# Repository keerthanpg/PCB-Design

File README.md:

# PCB-Design

Files for our implementation of an electronic 2DOF face tracker

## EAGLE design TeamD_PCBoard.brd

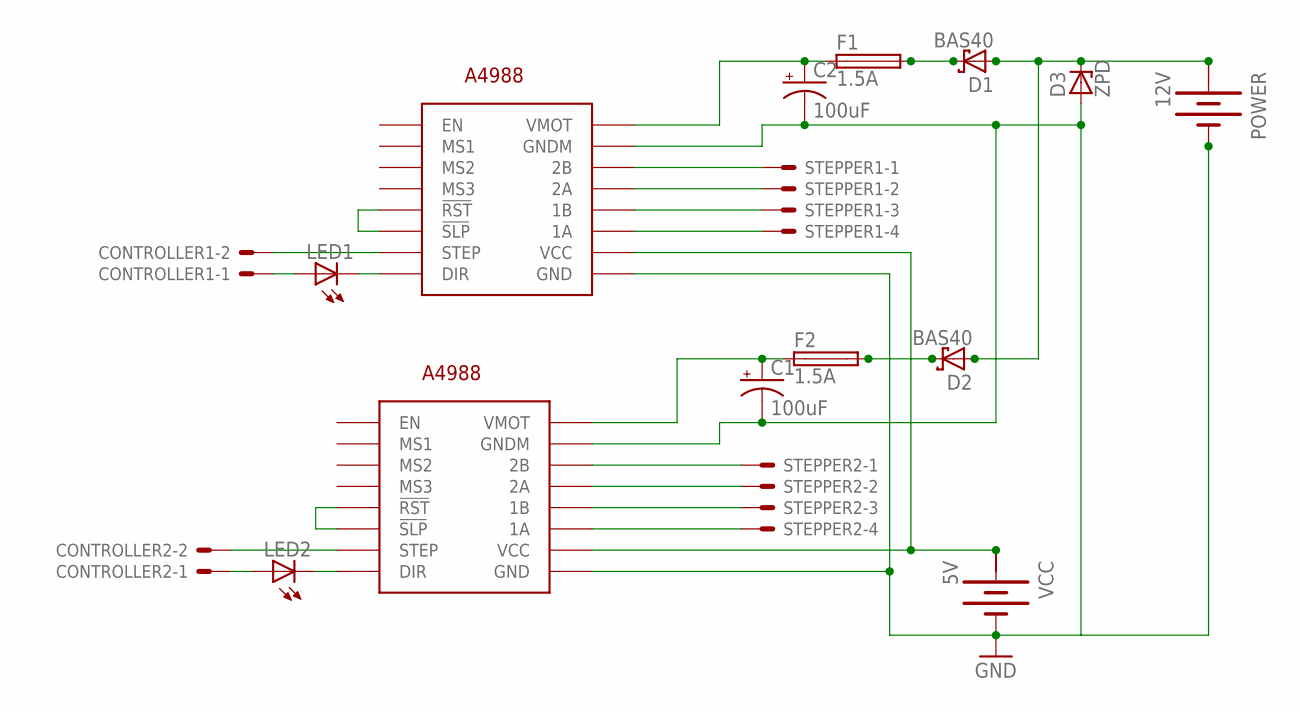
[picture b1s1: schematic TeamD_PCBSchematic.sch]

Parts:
C1, C2: 100uF; E15-5
CONTROLLER1, CONTROLLER2: 22-23-2021
D1, D2: BAS40; SOT23
D3: ZPD; DO35Z10
F1, F2: 1.5A; 19559
LED1, LED2: LED; SMARTLED-TTW
POWER: 12V; BATTERY
STEPPER1, STEPPER2: 22-23-2041
U$1, U$2: STEP-STICK
VCC: 5V; BATTERY

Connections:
+: POWER.+@1 (+), VCC.+@1 (+)
unnamed: CONTROLLER1.2, U$1.SPT (STEP)
unnamed: CONTROLLER2.2, U$2.SPT (STEP)
unnamed: CONTROLLER2.1, LED2.A@1 (A)
unnamed: U$1.RST (!RST), U$1.SLP (!SLP)
unnamed: U$2.RST (!RST), U$2.SLP (!SLP)
unnamed: STEPPER2.1, U$2.2B
unnamed: STEPPER2.2, U$2.2A
unnamed: STEPPER2.3, U$2.1B
unnamed: STEPPER2.4, U$2.1A
unnamed: STEPPER1.1, U$1.2B
unnamed: STEPPER1.2, U$1.2A
unnamed: STEPPER1.3, U$1.1B
unnamed: STEPPER1.4, U$1.1A
unnamed: D1.3 (C), F1.2
unnamed: LED1.C@1 (C), U$1.DIR
unnamed: LED2.C@1 (C), U$2.DIR
unnamed: C2.+, F1.1, U$1.VMOT
unnamed: C1.+, F2.1, U$2.VMOT
unnamed: U$1.VCC, U$2.VCC, VCC.+
unnamed: D2.3 (C), F2.2
unnamed: D1.1 (A), D2.1 (A), D3.C, POWER.+
unnamed: C1.-, C2.-, D3.A, POWER.-, U$1.GND, U$1.GNDM, U$2.GND, U$2.GNDM, VCC.-
S$1: CONTROLLER1.1, LED1.A@1 (A)

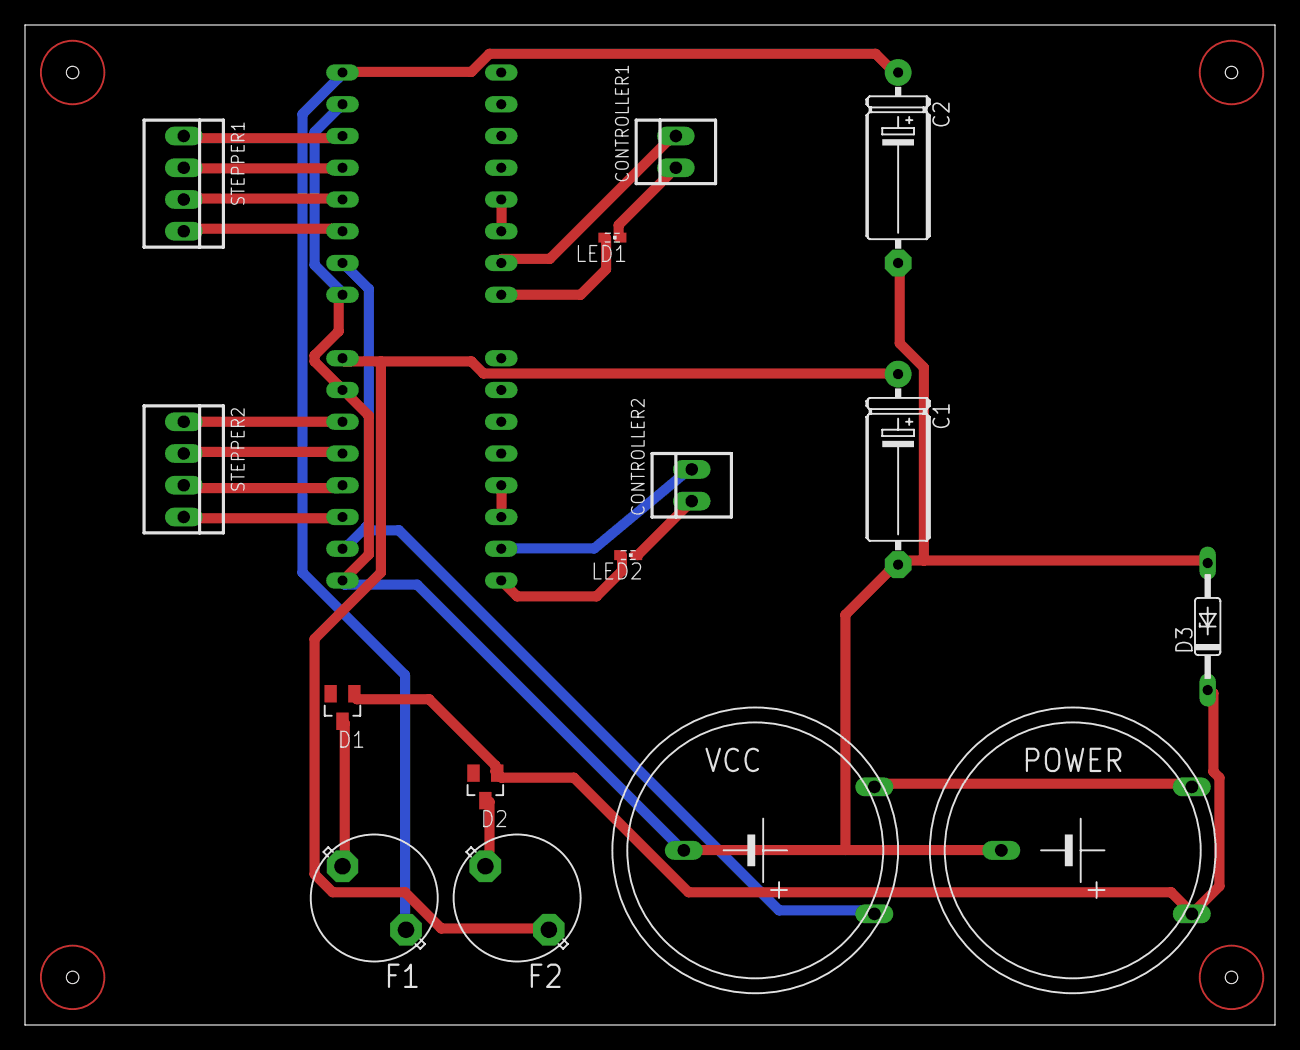
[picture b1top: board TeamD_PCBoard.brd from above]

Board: 2 copper layers, 100.0 x 80.0 mm, 17 parts (0 on the bottom side), 23 nets.
